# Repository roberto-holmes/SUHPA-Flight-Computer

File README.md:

# SUHPA Avionics

Currently divided into CRASH (Controls, Radio, and Avionics for Southampton HPA) that receives input from the pilot and sends it to Pod that controls the servos.

## Software
TODO:
- Varying frequency beep as trim value changes
- Accelerating trim input
- Add average update rate to display

Known issues:
- SD card doesn't reinitialize if it disconects as this would cause the device to only transmit packets every couple of seconds
- Packet loss is not representative of the number of packets being received by Pod as the ACK packages being sent back are the ones getting lost. Pod has to send them at a lower power for some reason causing this issue.

## Hardware

### CRASH 

v1.0
- Status: Completed
- Issues:
   * Stress relief holes for battery cables are too small
   * Middle support holes are not required
   * Circle cutout is not quite aligned
   * Square cutout could have more clearance on the left

### Pod
v1.0
- Status: Completed
- Issues: 
   * Short between 5v_Servo and GND at the BEC connector
   * Insufficient spacing between buzzer and balance connector
   * Balance connector keeps board powered (should be replaced with just measuring the voltage of V_bat)

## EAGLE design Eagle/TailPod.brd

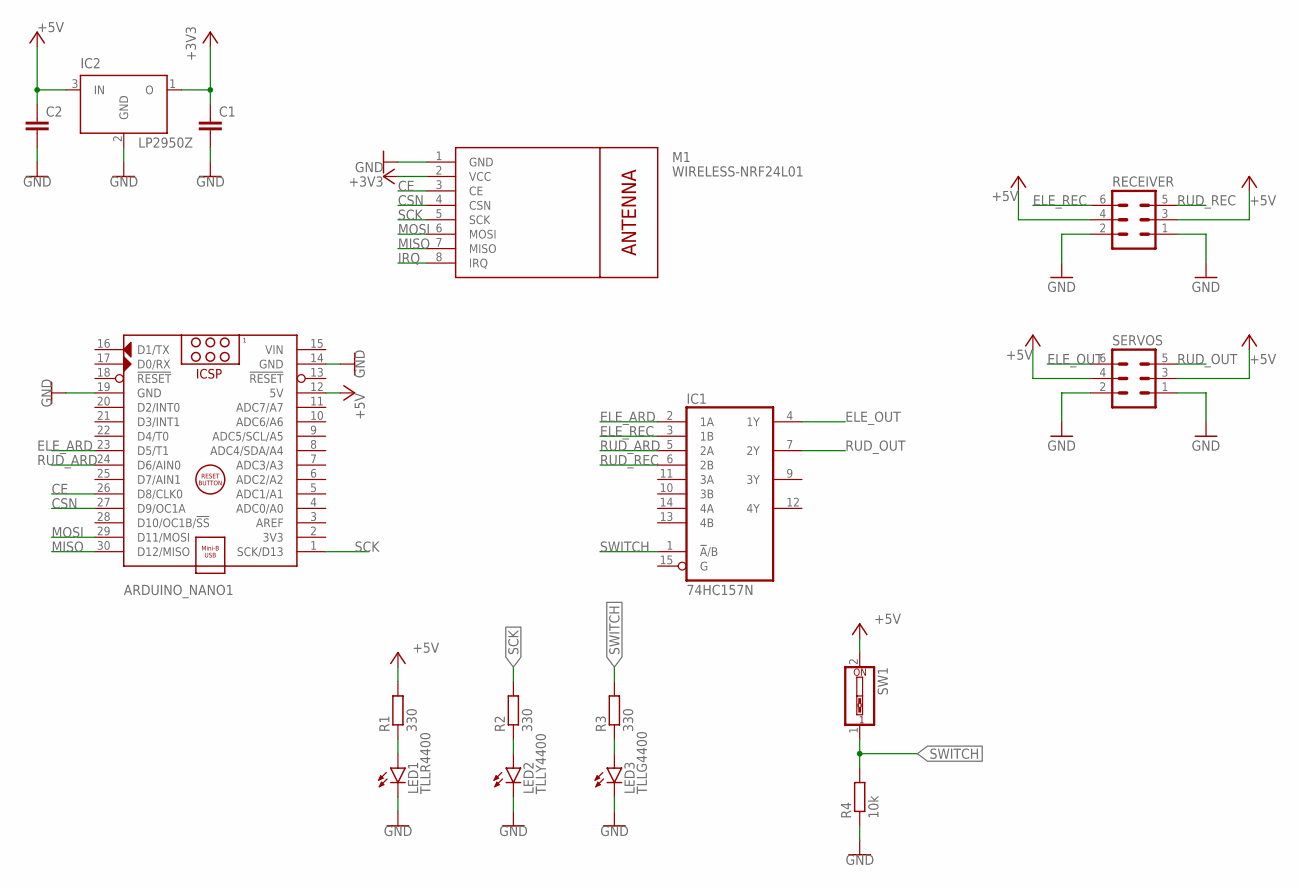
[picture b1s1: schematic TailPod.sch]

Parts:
ARDUINO_NANO1: ARDUINO_NANO
C1, C2: C2,5-3; C2.5-3
IC1: 74HC157N; DIL16
IC2: LP2950Z; TO92
LED1: TLLR4400; LED3MM
LED2: TLLY4400; LED3MM
LED3: TLLG4400; LED3MM
M1: WIRELESS-NRF24L01
R1, R2, R3: 330; 0204/7
R4: 10k; 0204/7
RECEIVER: MA03-2
SERVOS: MA03-2
SW1: SW_DIP-1; EDG-01

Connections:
+3V3: C1.1, IC2.1 (O), M1.2 (VCC)
+5V: ARDUINO_NANO1.12 (5V), C2.1, IC2.3 (IN), R1.2, RECEIVER.3, RECEIVER.4, SERVOS.3, SERVOS.4, SW1.2
CE: ARDUINO_NANO1.26 (D8/CLK0), M1.3 (CE)
CSN: ARDUINO_NANO1.27 (D9/OC1A), M1.4 (CSN)
ELE_ARD: ARDUINO_NANO1.23 (D5/T1), IC1.2 (1A)
ELE_OUT: IC1.4 (1Y), SERVOS.6
ELE_REC: IC1.3 (1B), RECEIVER.6
GND: ARDUINO_NANO1.14 (GND), ARDUINO_NANO1.19 (GND), C1.2, C2.2, IC1.8 (GND), IC2.2 (GND), LED1.K (C), LED2.K (C), LED3.K (C), M1.1 (GND), R4.1, RECEIVER.1, RECEIVER.2, SERVOS.1, SERVOS.2
IRQ: M1.8 (IRQ)
MISO: ARDUINO_NANO1.30 (D12/MISO), M1.7 (MISO)
MOSI: ARDUINO_NANO1.29 (D11/MOSI), M1.6 (MOSI)
unnamed: LED1.A, R1.1
unnamed: LED2.A, R2.1
unnamed: LED3.A, R3.1
RUD_ARD: ARDUINO_NANO1.24 (D6/AIN0), IC1.5 (2A)
RUD_OUT: IC1.7 (2Y), SERVOS.5
RUD_REC: IC1.6 (2B), RECEIVER.5
SCK: ARDUINO_NANO1.1 (SCK/D13), M1.5 (SCK), R2.2
SWITCH: IC1.1 (!A!/B), R3.2, R4.2, SW1.1
VCC: IC1.16 (VCC)
VIN: ARDUINO_NANO1.15 (VIN)

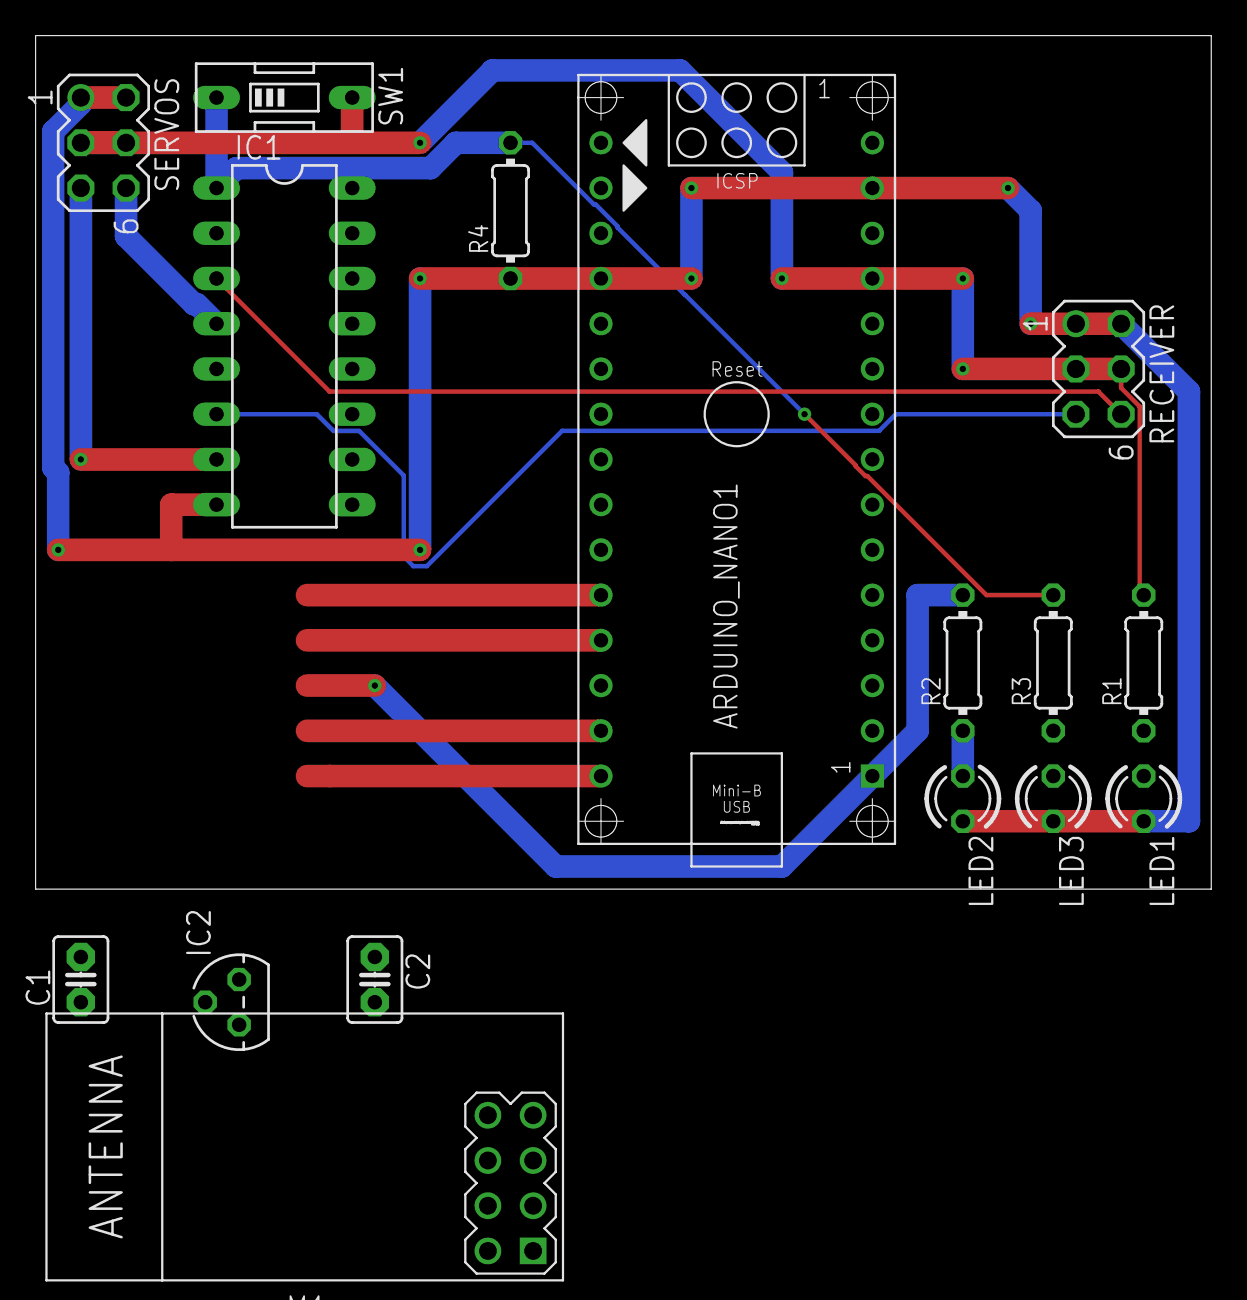
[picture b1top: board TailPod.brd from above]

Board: 2 copper layers, 66.0 x 47.9 mm, 16 parts (0 on the bottom side), 18 nets.

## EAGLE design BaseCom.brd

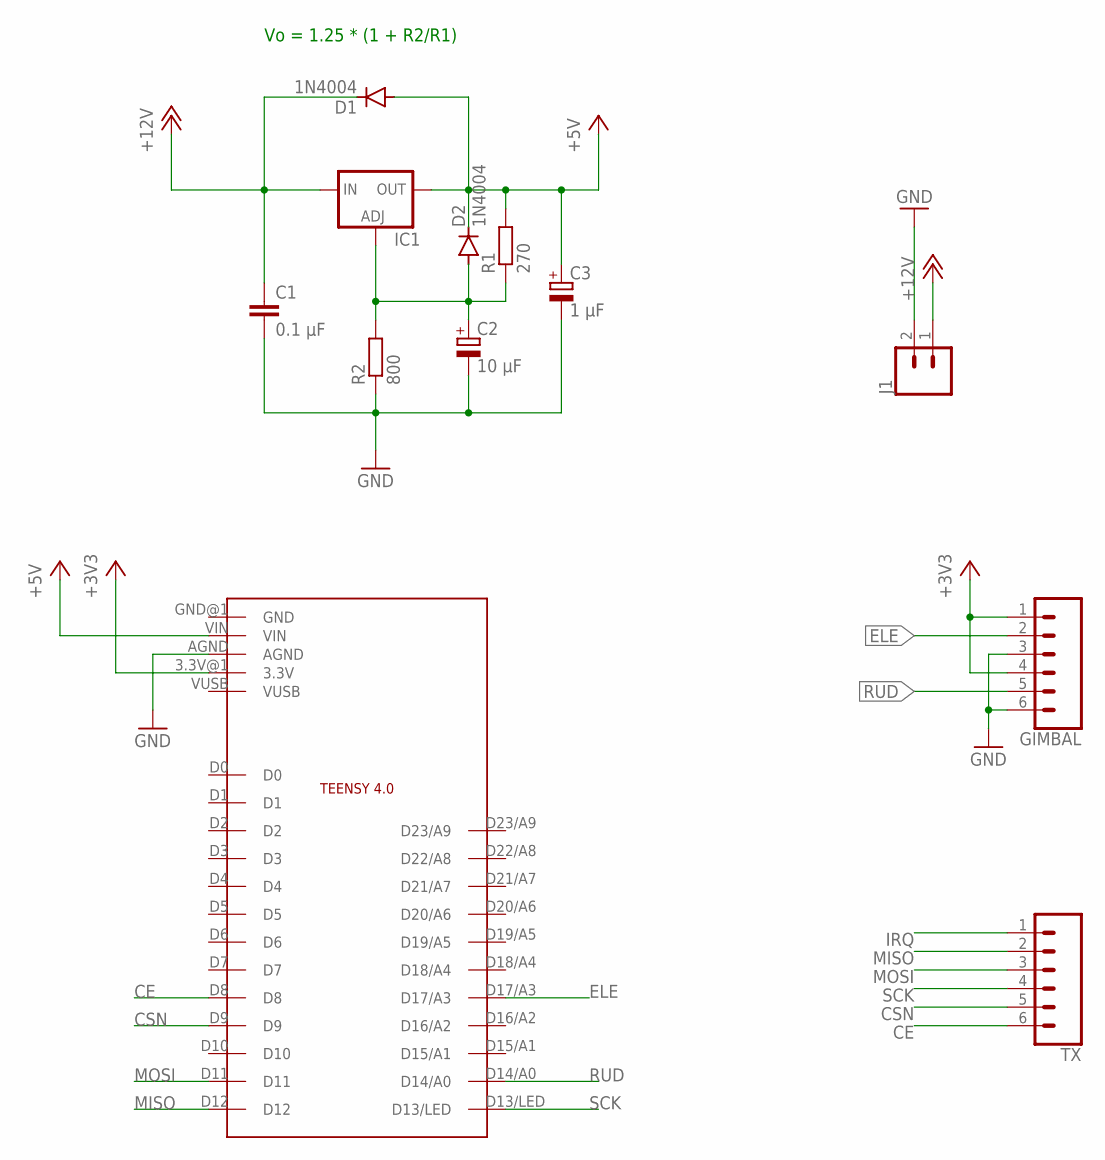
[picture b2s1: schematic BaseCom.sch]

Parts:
C1: 0.1 µF; C2.5-5
C2: 10 µF; E1,8-4
C3: 1 µF; E1,8-4
D1, D2: 1N4004; DO41-10
GIMBAL: CONN_06SILK_FEMALE_PTH; 1X06
IC1: LM317TL; 317TL
J1: CONN_02POLAR; MOLEX-1X2
R1: 270; 0204/7
R2: 800; 0204/7
TX: CONN_06SILK_FEMALE_PTH; 1X06
U$1: TEENSY4.0_SIMPLE

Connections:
+3V3: GIMBAL.1, GIMBAL.4, U$1.3.3V@1 (3.3V)
+5V: C3.+, D1.A, D2.C, IC1.2 (OUT), R1.2, U$1.VIN
+12V: C1.1, D1.C, IC1.3 (IN), J1.1
CE: TX.6, U$1.D8
CSN: TX.5, U$1.D9
ELE: GIMBAL.2, U$1.D17/A3
GND: C1.2, C2.-, C3.-, GIMBAL.3, GIMBAL.6, J1.2, R2.1, U$1.AGND
IRQ: TX.1
MISO: TX.2, U$1.D12
MOSI: TX.3, U$1.D11
unnamed: C2.+, D2.A, IC1.1 (ADJ), R1.1, R2.2
RUD: GIMBAL.5, U$1.D14/A0
SCK: TX.4, U$1.D13/LED

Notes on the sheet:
Vo = 1.25 * (1 + R2/R1)

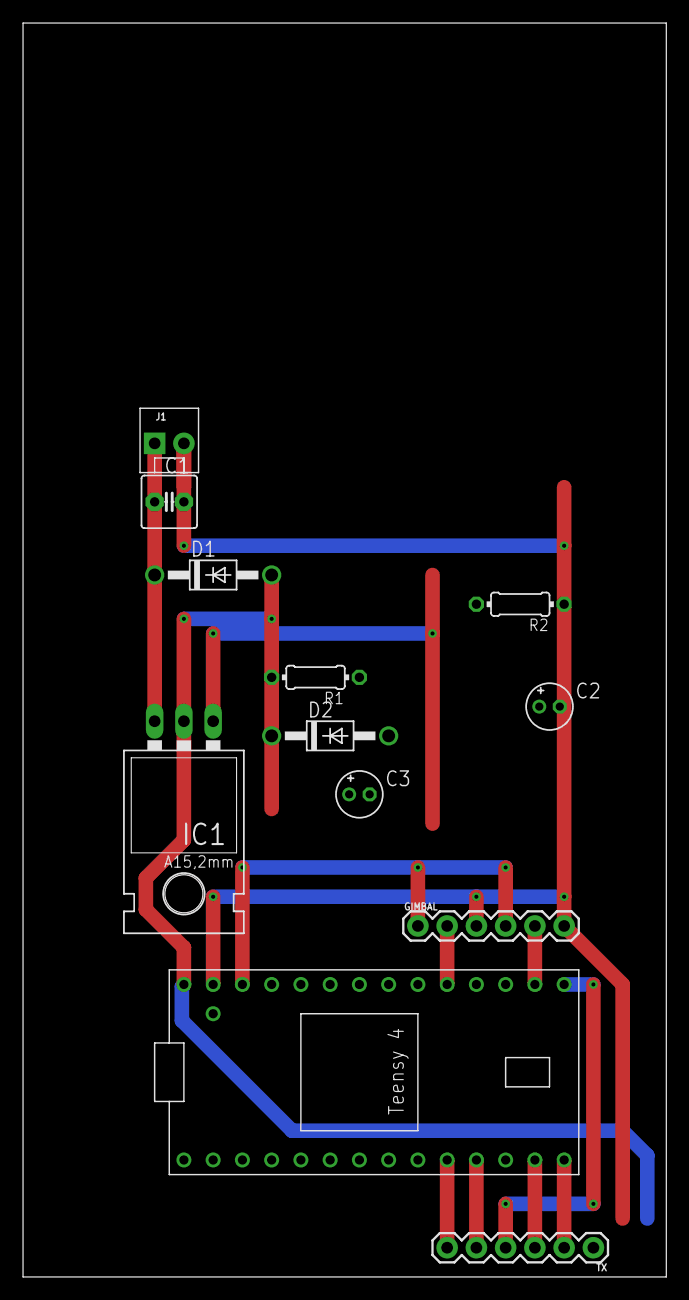
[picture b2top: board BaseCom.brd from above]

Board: 2 copper layers, 55.9 x 108.9 mm, 12 parts (0 on the bottom side), 12 nets.

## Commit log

2020-03-18 Added stripboard designs
2020-05-29 Designed Pod v1 in Altium. Reorganised stripboard designs into EAGLE folder.
2020-06-22 Fixed short between 5V_servo and GND present on v1.0
2020-06-22 Updated README and gitignore
2020-11-25 Added dimensions and decriptions to Pod PCB document. Created STEP file of the Gimbal.
2020-11-27 Added basic software to read stick and trim inputs and transmit them to the Pod computer
2020-11-27 Made modifications to the Adafruit SSD1306 library to allow it to work for the SSD1362. This does come with a number of bugs and is currently not fully functional.
2020-11-28 Improved processing of stick inputs and properly constrained PWM outputs. Increased trim hold delay when it is 0.
2020-11-28 Added frame synchronisation test.
2020-11-28 Added SSD1362 datasheet.
2020-11-28 Fixed rendering images to display.
2020-11-28 Added SUHPA logo.
2020-11-28 Code cleanup
2020-12-03 Added position of stick in X, Y and XY plot on display.
2020-12-03 Fixed stick input direction scaling.
2020-12-03 Added actual range of PWM values
2020-12-04 Added functionality to measure battery voltage
2020-12-05 Update README.md
    Added TODO and CRASH board, including hardware issues
2020-12-05 Update README.md
    Added EEPROM functionality to TODO
2020-12-05 Update README.md
    Added screensaver to TODO
2020-12-08 Added battery level indicator bar and value to display.
2020-12-08 Added storage of trim setting in EEPROM.
2020-12-08 Made beep asynchronous.
2021-01-28 Implemented acknowledgement (ack) packets and packet loss and ping metrics. Replaced delay() with an interval. Packet loss is currently not necessarily indicative of the main packet because the ACK i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
2021-01-28 Updated TODO
2021-02-06 Added reading and storage of sensor values to csv files.
2021-02-06 Added ping, packet loss and sd connection status to display.
2021-02-06 Added separate timer for when the display gets updated.
2021-02-06 Made screen turn off after 30 seconds to prevent damage to the OLED. Also changed ping to be in ms, rather than us.
2021-02-06 Updated readme.
2021-02-06 Stopped SD card reinitialization if it disconnects. This means the device needs to be restarted if the SD card disconnects. However, doing this prevents the device lagging due to the time it takes to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
2021-02-08 Inverted inputs, increased number of trim steps to 100, added warning light if radio fails to begin, changed radio address, updated BMP3XX library to 2.0.2 and changed startNewFile() to void.
2021-02-08 Updated TODO and included known software issues that will not be addressed for now.
2021-02-08 Added units to csv file of stored data. Also changed to storing pressure, rather than altitude.
2021-02-08 Improved performance to make sure things update closer to the rate they should.
2021-02-08 Fixed trim still being inverted.
2021-02-08 Added trim value to display. Also capped trim values at +-99 rather than +-100, to make displaying it easier.
2021-07-24 vertical stick: sensivity changed and inverted due to the flip of the elevator
2021-08-01 Added Crash flight computer Altium files.

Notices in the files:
parts and their libraries:
SparkFun-Connectors: Licensing: Creative Commons ShareAlike 4.0 International - https://creativecommons.org/licenses/by-sa/4.0
diy-modules: Released under the Creative Commons Attribution 4.0 International License: http://creativecommons.org/licenses/by/4.0
